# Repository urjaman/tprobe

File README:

This is a logic probe from an ATtiny85V thingy,
just for the lulz.

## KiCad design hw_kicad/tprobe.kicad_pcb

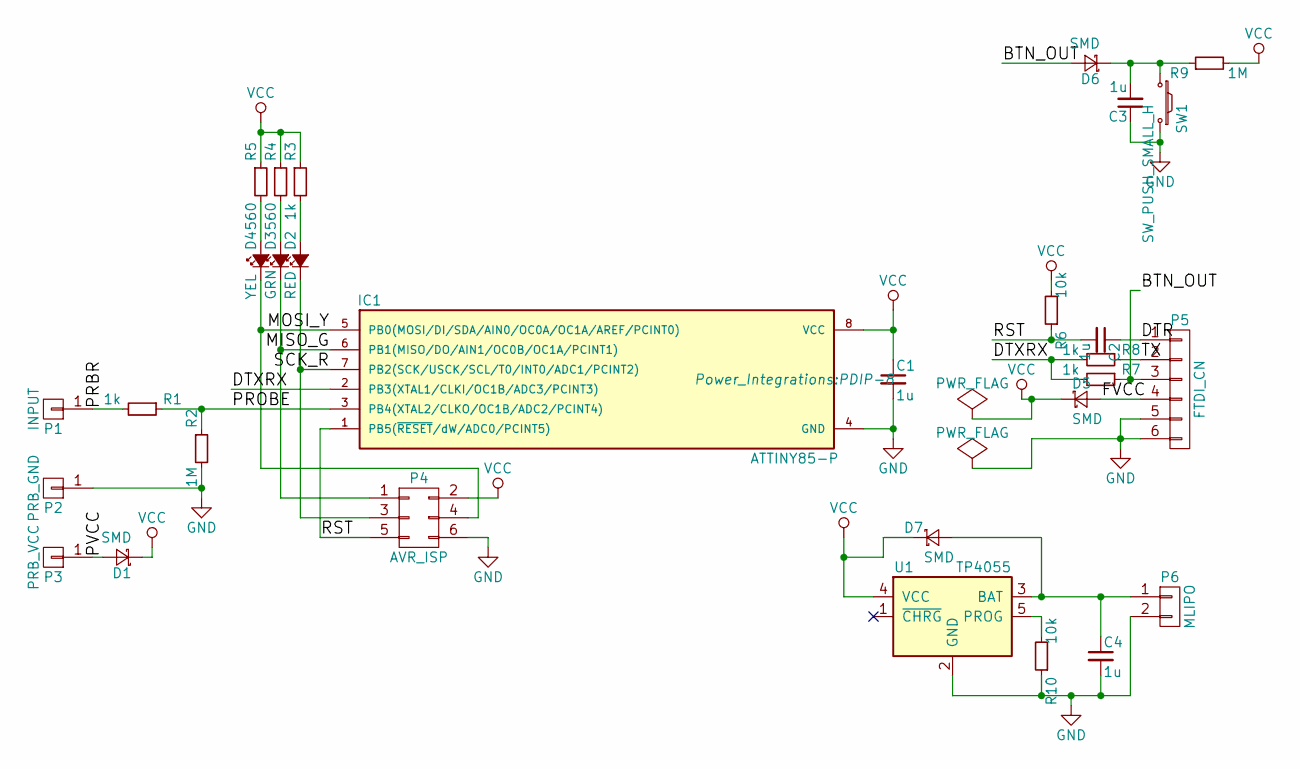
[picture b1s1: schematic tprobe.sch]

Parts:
C1, C2, C3, C4: 1u; C_0603_HandSoldering
D1, D5, D6, D7: SMD; SOD-323_HandSoldering
D2: RED; LED-3MM
D3: GRN; LED-3MM
D4: YEL; LED-3MM
IC1: ATTINY85-P; PDIP-8
P1: INPUT; SolderWirePad_single_2mmDrill
P2: PRB_GND; SolderWirePad_single_2mmDrill
P3: PRB_VCC; SolderWirePad_single_2mmDrill
P4: AVR_ISP; Pin_Header_Straight_2x03
P5: FTDI_CN; Socket_Strip_Angled_1x06
P6: MLIPO; Pin_Header_Straight_1x02
R1, R3, R7, R8: 1k; R_0603_HandSoldering
R2, R9: 1M; R_0603_HandSoldering
R4, R5: 560; R_0603_HandSoldering
R6, R10: 10k; R_0603_HandSoldering
SW1: SW_PUSH_SMALL_H; SW_PUSH_6mm
U1: TP4055; SOT-23-5

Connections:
/BTN_OUT: D6.2 (A), P5.3, R7.1
/DTR: C2.1, P5.1
/DTXRX: IC1.2 (PB3(XTAL1/CLKI/OC1B/ADC3/PCINT3)), R7.2, R8.2
/FVCC: D5.2 (A), P5.4
/MISO_G: D3.1 (K), IC1.6 (PB1(MISO/DO/AIN1/OC0B/OC1A/PCINT1)), P4.1
/MOSI_Y: D4.1 (K), IC1.5 (PB0(MOSI/DI/SDA/AIN0/OC0A/OC1A/AREF/PCI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), P4.4
/PRBR: P1.1, R1.2
/PROBE: IC1.3 (PB4(XTAL2/CLKO/OC1B/ADC2/PCINT4)), R1.1, R2.1
/PVCC: D1.2 (A), P3.1
/RST: C2.2, IC1.1 (PB5(~RESET~/dW/ADC0/PCINT5)), P4.5, R6.1
/SCK_R: D2.1 (K), IC1.7 (PB2(SCK/USCK/SCL/T0/INT0/ADC1/PCINT2)), P4.3
/TX: P5.2, R8.1
GND: C1.2, C3.1, C4.2, IC1.4 (GND), P2.1, P4.6, P5.5, P5.6, P6.2, R2.2, R10.1, SW1.2, U1.2 (GND)
unnamed: C3.2, D6.1 (K), R9.1, SW1.1
unnamed: C4.1, D7.2 (A), P6.1, U1.3 (BAT)
unnamed: D2.2 (A), R3.2
unnamed: D3.2 (A), R4.2
unnamed: D4.2 (A), R5.2
unnamed: R10.2, U1.5 (PROG)
VCC: C1.1, D1.1 (K), D5.1 (K), D7.1 (K), IC1.8 (VCC), P4.2, R3.1, R4.1, R5.1, R6.2, R9.2, U1.4 (VCC)

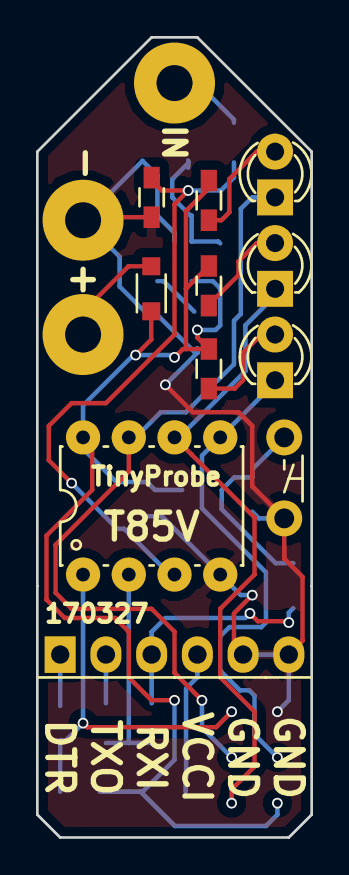
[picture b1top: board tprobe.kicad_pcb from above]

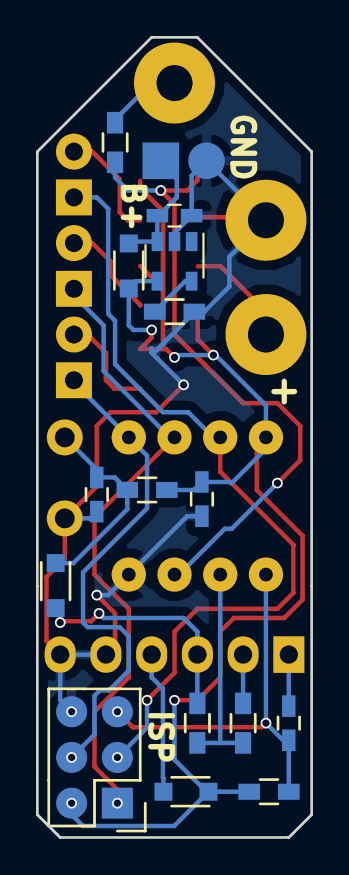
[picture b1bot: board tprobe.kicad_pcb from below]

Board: 2 copper layers, 15.2 x 44.5 mm, 30 parts (16 on the bottom side), 20 nets.

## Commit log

2017-03-19 hw only initial commit
2017-03-22 first software thats programmable easily :)
2017-03-22 fricking make sure we reset the thing
2017-03-22 WDT-based sleepy timer stuff tested
2017-03-22 first probe-implementing code
2017-03-22 docz
2017-03-24 change the interrupts to asm
2017-03-26 hacky test (yeah, stdio is big :P)
2017-03-27 It deserves a real li-ion charger :)
2017-03-28 sleepier adc
2017-03-28 get rid of the stdio :P
    other prep too...
2018-04-09 fix alignment of buffers in probeuart.S
2018-04-09 adjust for C201
2018-04-09 Only UART tx if we're powered
    this should optimize idle battery runtime...
2018-04-10 Implement tri-tap menu and basic alternative mode switching
    No alternative modes have been implemented yet, so
    it's only a toy menu and a mode that disables the logic probe
    Also added a brainstorming textfile about the menu, so maybe
    the usage logic goes through :P
2018-04-10 Implement a deep sleep mode
    It disables pretty much everything except the async pin change interrupts,
    and should bring the AVR down to the 1µA range, in theory.
    Note: BOD sleep wasnt planned to be used with these fuse settings,
    and officially it might not come out of the sleep sanely - but
    i dont really care if it ends up resetting or something, and well
    we are disabling the brownout detector anyways... in my tests
2018-04-11 Implement supertimer, altmode timeout and some test-like modes
2018-04-11 Add a funsie 'Flashlight' mode 5
    I just need a power-burning dummy mode and it's kinda fun to
    turn all the LEDs on so ... :P
2018-04-11 Add an activity timer to deep sleep the thing after 3 hours unused
    I mean, in theory this should make the battery last pretty much
    forever (11 years lol) if you forget the thingy somewhere. In theory.
2018-04-14 Add some inactivity diagnostics and a generic diagnostic mode
2018-04-14 Disable probe char (with 'N' to signify no data) when probe is disabled
2018-04-17 Implement alt mode 4: 15.625Hz (nominal) square wave output
    also make mode 5 transmit a steady 1,
    it kinda makes sense with the flashlight :P
2018-04-17 fix the UART if switching between modes
2018-04-18 Reorganize UART tx, implement ADC alt. modes
2018-06-30 random stuff i left behind ...
2018-10-13 fix termios bug in serialprogrammer, clean it up a little
2018-10-13 Implement sub-modes to free some main modes for more functionality later
    The alt mode map is now like this:
    - mode 1: ADC readouts
    - submode 1: full range (1.8/3.3/5V check)
    - submode 2: low range (1.5 V battery check)
    - submode 3: high range (Lipo battery check)
    - mode 2: free
2018-10-14 Implement diode test mode (also slightly optimize ADC)
    next: autocalibrating diode test mode
    ... i'm thinking you'd just switch to submode 2
    and hold the probes together and it'd count down
    a few seconds on the LEDs and then set the calib
    and switch back to submode 1.
2018-10-14 Implemented runtime calibration of the diodetest
    The thing is able to tell a short from a diode and a LED from a traditional diode,
    and also very crudely approximate (+- 20% ?) resistor values
    in the 200 ohm ... 330 k range (those only over serial, mostly for debug)
    Anyways the calibration is submode 2 of mode 2, and it
    only needs you to hold the probe to ground for a sec and then
    let go for another.
2018-10-14 Add the docs i wrote when implementing diode test
2018-10-15 optimize code size for integer output functions
2018-10-18 Implement higher-speed PWM submodes of previous mode 4 as mode 3
    Mode 1 is still the slow sleepy 15.625 Hz (without timer) :)
2018-10-18 implement submode counts in a table, and functionalize things
    also: an "int" (16-bit signed) numeric parser and a test command
    for that
2018-10-20 WIP cal stuff
2018-10-21 Make the soft uart adaptive to bit edges
    Most of the commands and things you might want to send
    to the device have an edge in them, so this should
    help if your AVR RC OSC happens to be near the tolerance
    for an UART, even if it's not a perfect solution
    - there is calibration for that :P
    (TODO still on saving that, lol)
2018-10-21 un-break the PWM, add adjustable timeout to numeric entry
2018-10-21 show less useless info on the line
2018-10-22 Implement ohm magnitude readout on the LEDs
    That is mode 2 submode 2, moved the diode/ohm mode
    calibration to submode 3.
    Now you can have some idea of the ohms even without UART :P
2018-10-22 simplify setup_pwm
2018-10-22 set attribute OS_main to main()
2018-10-23 add variable duty PWM ability
2020-09-17 Update menu.txt to contain the actual menu structure
    This is mostly for me so that i don't need to figure out
    how to use this from the source code :)
